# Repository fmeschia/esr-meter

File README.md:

ESR Meter
=========
An Arduino-based battery internal resistance meter.

Introduction
------------
This device measures the internal resistance of a battery by measuring the voltage difference at the battery terminals when a load is applied and then removed. By measuring the difference in voltage and the difference in current, the resistance is readily determined via Ohm's law.

Design goals
------------
* Measure internal resistance for batteries with voltages ranging from a 4-cell NiXX to a 4S LiPo pack
* Resistance range: 1 to 1000 mOhm
* Ability to do 4-wire measurements
* Target precision: 2% ± 1 LSB
* Ability to draw power either from the battery under test, or from a separate battery
* Powered by the Atmel ATMega328P microcontroller (so that it can be prototyped with Arduino)
* Low cost!

Design
------

This device measures the internal resistance by using Ohm's law: R = ∆V/∆I. The battery is first connected to a load, then the load is removed. The voltage at the battery teminals is measured just before removing the load, and just after the load is removed. The current drawn from the battery is also measured, almost simultaneously with the two voltage measurements.

Voltage and current measurement is performed using a 4-wire (Kelvin) technique: current is measured by a sensing resistor along the "hot" high-current path which connects the battery to the load, and voltage is sensed through two "cold" leads, that carry no current. This also allows for internal resistance measurement of the individual cells in a multi-cell battery, as long as the individual cell voltages are available at a balance tap.

One of the problems that must be solved is how to measure voltages (like the two battery under test terminals) which may exceed the ADC reference voltage. The ATMega328P microcontroller can be powered with 5.5V maximum, so if we were to do a direct measurement (battery terminals direct to ADC inputs) we would be only be able to measure a 4-cell NiXX battery... if it's not fully charged.

One possibility to overcome this problem would be to use differential analog amplifiers to bring the voltages within the measurement range. The gain and the baseline of the amplifiers could be adjusted by the micro with digital potentiometers, to adapt to different battery voltages. The drawback is the number of additional components, which influences the cost of the device.

Instead of going this route, we decided to use "AC coupling". The voltages sensed at the battery terminals are filtered through one-pole (RC) low-pass filters, so that their DC component is removed.

If the time constant of the fiter is sufficiently long compared to the load-switching-to-measurement delay, we would only measure the actual change in voltage, with negligible error (compare, in the scope plot below, the yellow DC-coupled voltage at the positive battery terminal with the green AC-coupled signal: 1 ms after the load is switched off, when the measurement is taken, the AC-coupled signal is a very faithful estimate of the voltage difference at the battery terminal).

 vs. AC (green) measure of ∆V")

In order to ensure reasonable precision with low cost, we also decided to reference the ADCs to the internal bandgap voltage reference of the micro. This means that, if we want to meet the 1 Ohm maximum range stated in the design goals, we need to draw less than about 1.1 A (we designed the prototype for 0.8 A).

Such an electronic load can be conveniently built with a LM317 regulator used as a current source. This will be the heart of the "hot" loop. Additionally, the hot loop will also include: 

*  a Schottky diode for protection against reverse polarity
*  an n-channel MOSFET used as a switch
*  a 1 Ohm, 1% precision, current sensing resistor

Mainly because of the LM317 dropout characteristics, the minimum voltage that needs to be applied to the hot loop if we want the design current draw is about 4 V. A lower voltage would lead to a lower current figure, as long as it is enough to correctly bias the BJTs inside the LM317 (after that, the device won't work any more). We tested the circuit with a single LiPo cell discharged to 3.5V, without any problem.

The hot loop is switched on and off by the microcontroller, which we decided to power at 3.3 V with an external clock runing at 8 MHz. The program running on the micro switches on the load for 500 ms, then switches it off for 1500 ms, before starting a new cycle. In this way, the 25% duty cycle helps in keeping the average power dissipation acceptable for a LM317 with a passive heat sink, even when sinking current from a 4S LiPo battery.

The microcontroller also drives a standard HD44780 2x16 parallel-interface LCD display module, to output the result of the internal resistance computation at the end of each 2-second measurement cycle. The measurement is automatically refreshed every 2 seconds, for as long as the unit is powered. 

Power for the circuit may come either directly from the battery under test (requires the use of a LDO regulator and a 3.3 V display module), or from a separate battery.

Making it
---------
The project includes Eagle files for both the schematics and the board. The board was designed as a 2-layer PCB with the same 80x36 mm form factor used by standard 2x16 LCD modules, and with the same mounting hole pattern, so that it can be stacked using 1" standoffs.

The Bill of Materials is also included in the project. Here are some component selection notes:

* it is important for precision to use a 1 Ohm, 1% current sensing resistor (R8 in the schematic);
* the reverse-polarity protection diode used in the hot loop (D1 in the schematic) can be replaced with a more common 1N4001 diode, but this increases the voltage drop along the hot loop and may create problems to the LM317 electronic load. If you plan to build this circuit for single-LiPo or 4S NiXX use, it is best to stick with a Schottky diode;
* the Q1 n-channel MOSFET is not critical, as long as it can reliably switch completely on with a 3.3 V gate-to-source voltage. For single-LiPo or 4 NiXX operation, a low "on" drain-to-source resistance is advisable. The FQP30N06L we suggest in the schematic has just 0.035 Ohms of forward resistance when fully "on".
* any 3.3 V low-dropout linear regulator can be used for single-battery operation. The board is designed for the footprint of a L4931. 
* the LM317 used as a current source requires a heat sink for reliable operation. The sink resistor, R1, will dissipate 1 W and must therefore be sized accordingly.

Other notes:

* the board includes two jumper headers. One, labeled "JP3", determines whether the board will be powered from the battery under test (if closed), or from an external battery (if open). In the latter case, a suitable power source must be provided at the via labeled "VCC-ALT".
* the other jumper, JP1, if closed forces the software running in the ATMega328P to show debug information (sensed voltages and currents) in addition to the resistance value.
* another header, JP2, provides an interface to the serial port of the ATMega328P. It is pin-compatible (but pay attention to the correct orientation!) with the FTDI FT232L breakout board offered by Sparkfun (https://www.sparkfun.com/products/9873). The serial port can be used to upload the software into the microcontroller if an Arduino bootloader is used.

The microcontroller must be programmed with the software found in the esr_meter directory. First the software must be compiled within the Arduino IDE, then it must be burned into the ATmega328P flash memory. There are essentially two options for that:

* if you use a microcontroller with a pre-burned Arduino bootloader, you can install the chip in the PCB, and then program it via the JP2 serial port;
* if your microcontroller doesn't have an Arduino bootleader yet, you need to use an ISP programmer (there are several options –- see https://www.arduino.cc/en/Main/Standalone for example) and burn the Arduino bootloader, then you can upload the software via the JP2 serial port.

Assembly notes:

* the LCD module is to be connected to the board with a short length of 6-lead ribbon cable. The 6 leftmost pins of JP4 go to pins 1 to 6 on the LCD module, and the 6 rightmost pins go to pins 11 to 16.
* the battery under test is to be connected to the "hot" loop through the two plated holes labeled BATT+ and BATT- on the board, of course while respecting the polarity, using two suitable wires; the holes should be able to accommodate up to AWG16. The two voltage sense leads will be soldered to the plated holes labeled S+ and S-; polarity in that case is not important, as the software can accommodate reverse polarity.
* The voltage sense leads do not necessarily need to be soldered to the battery connectors. For multiple-cell LiPo use, they can be soldered to a suitable pitch 2-pin header to sense the individual cells at the balancing connector (see picture below).

The following are some pictures of a specimen of the device:

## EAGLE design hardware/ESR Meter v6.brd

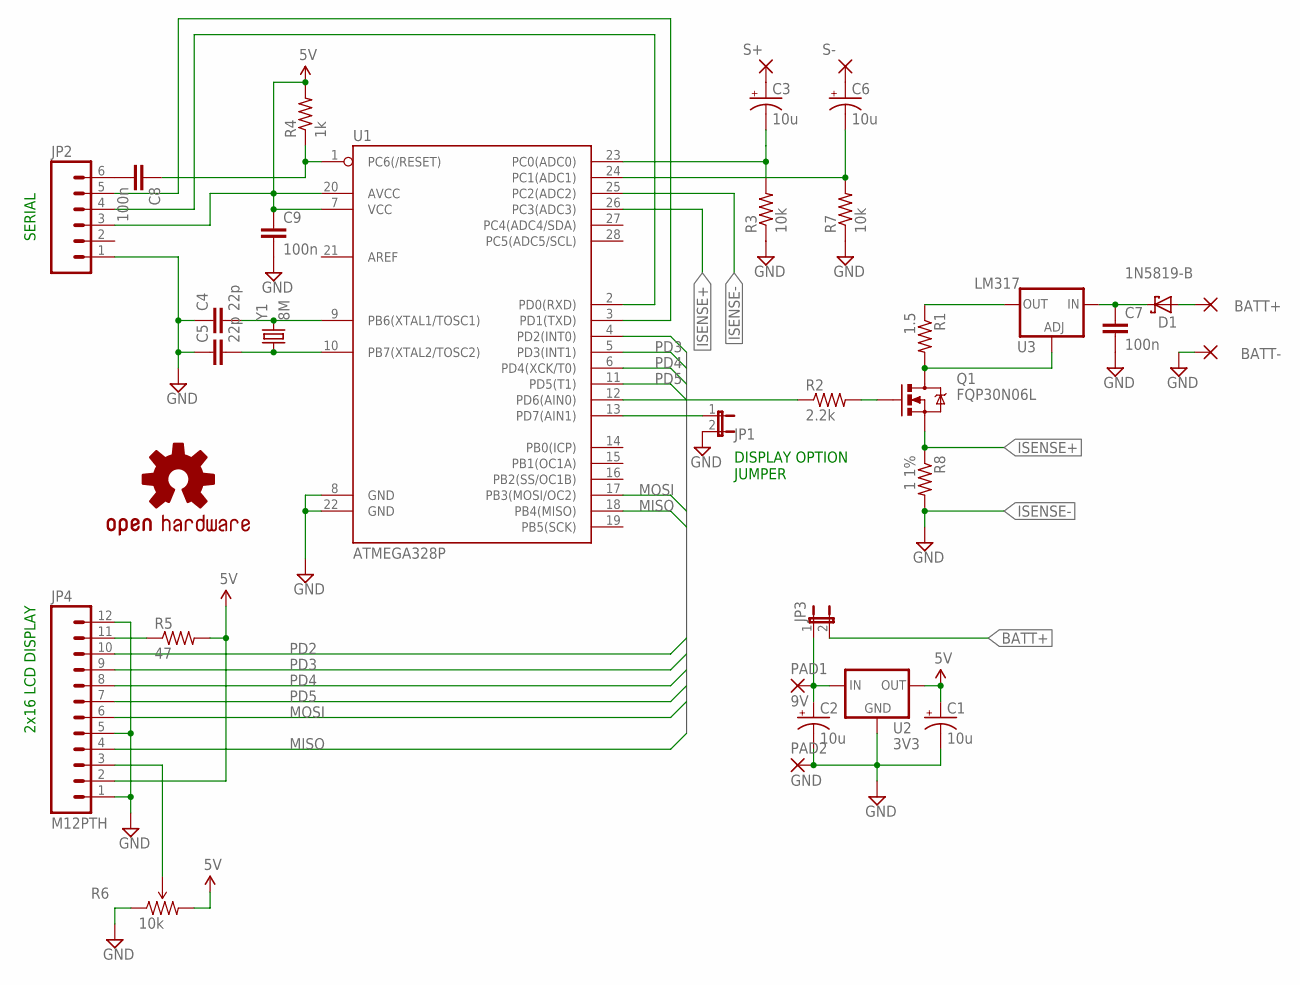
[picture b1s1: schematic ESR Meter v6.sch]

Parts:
BATT+: WIREPAD4,16O1,6; 4,16O1,6
BATT-: WIREPAD4,16O1,6; 4,16O1,6
C1, C2, C3, C6: 10u; CPOL-RADIAL-10UF-25V
C4, C5: 22p; CAP-PTH-SMALLEZ
C7, C8, C9: 100n; CAP-PTH-SMALLEZ
D1: 1N5819-B; DO41-7.6
JP1, JP3: JUMPER-2PTH; 1X02
JP2: M06SILK_FEMALE_PTH; 1X06
JP4: M12PTH; 1X12
LOGO1: OSHW-LOGOM; OSHW-LOGO-M
PAD1: 9V; 1,6/0,9
PAD2: GND; 1,6/0,9
Q1: FQP30N06L; TO220V
R1: 1.5; 0617V
R2: 2.2k; 0207/10
R3, R7: 10k; 0207/10
R4: 1k; 0207/10
R5: 47; 0207/10
R6: 10k; 3386U
R8: 1 1%; 0617V
S+: SENSE; 2,15/1,0
S-: SENSE; 2,15/1,0
U1: ATMEGA328P; DIL28-3
U2: 3V3; L4931
U3: LM317; TO220-ADJ
Y1: 8M; HC49US

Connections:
5V: C1.1 (+), C9.1, JP2.3, JP4.2, R4.2, R5.2, R6.3 (CW), U1.7 (VCC), U1.20 (AVCC), U2.OUT
BATT+: BATT+.1, D1.A, JP3.2
GND: BATT-.1, C1.2 (-), C2.2 (-), C4.1, C5.1, C7.2, C9.2, JP1.2, JP2.1, JP4.1, JP4.5, JP4.12, PAD2.1, R3.1, R6.1 (CCW), R7.1, R8.2, U1.8 (GND), U1.22 (GND), U2.GND
ISENSE+: Q1.3 (S), R8.1, U1.26 (PC3(ADC3))
ISENSE-: U1.25 (PC2(ADC2))
MISO: JP4.4, U1.18 (PB4(MISO))
MOSI: JP4.6, U1.17 (PB3(MOSI/OC2))
unnamed: Q1.1 (G), R2.2
unnamed: Q1.2 (D), R1.2, U3.ADJ
unnamed: R2.1, U1.12 (PD6(AIN0))
unnamed: C3.2 (-), R3.2, U1.23 (PC0(ADC0))
unnamed: C2.1 (+), JP3.1, PAD1.1, U2.IN
unnamed: C4.2, U1.9 (PB6(XTAL1/TOSC1)), Y1.2
unnamed: C5.2, U1.10 (PB7(XTAL2/TOSC2)), Y1.1
unnamed: JP4.3, R6.2 (WIPER)
unnamed: C8.2, JP2.6
unnamed: JP2.5, U1.3 (PD1(TXD))
unnamed: JP2.4, U1.2 (PD0(RXD))
unnamed: C3.1 (+), S+.1
unnamed: JP4.11, R5.1
unnamed: C6.1 (+), S-.1
unnamed: JP1.1, U1.13 (PD7(AIN1))
unnamed: C6.2 (-), R7.2, U1.24 (PC1(ADC1))
unnamed: R1.1, U3.OUT
unnamed: C7.1, D1.C, U3.IN
PD2: JP4.10, U1.4 (PD2(INT0))
PD3: JP4.9, U1.5 (PD3(INT1))
PD4: JP4.8, U1.6 (PD4(XCK/T0))
PD5: JP4.7, U1.11 (PD5(T1))
RESET: C8.1, R4.1, U1.1 (PC6(/RESET))

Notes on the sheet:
2x16 LCD DISPLAY
SERIAL
DISPLAY OPTION JUMPER

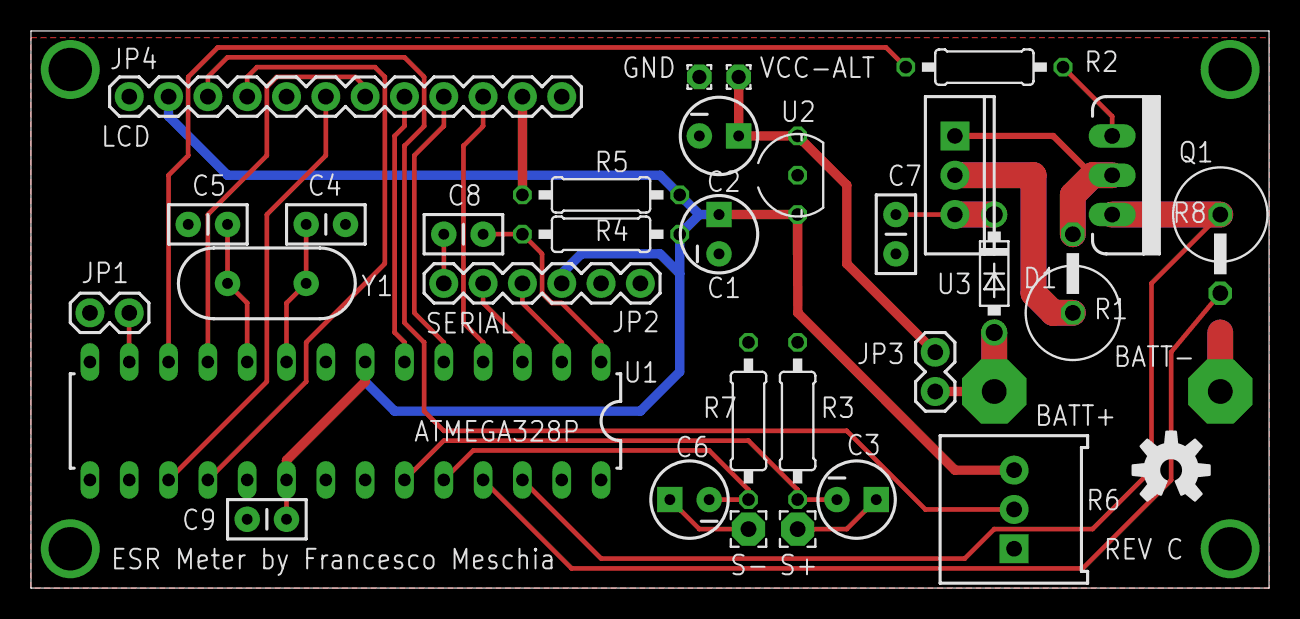
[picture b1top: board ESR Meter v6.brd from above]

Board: 2 copper layers, 80.0 x 36.0 mm, 34 parts (0 on the bottom side), 29 nets.

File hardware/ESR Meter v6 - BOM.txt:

Partlist exported from /Users/franz/Development/Arduino/esr-meter/hardware/ESR Meter v6.sch at 4/2/16 10:34 AM

Part  Value           Device                   Package              Description                                                                                                                                                                                                        PROD_ID    
C1    10u             CAP_POLPTH2              CPOL-RADIAL-10UF-25V Capacitor Polarized                                                                                                                                                                                                           
C2    10u             CAP_POLPTH2              CPOL-RADIAL-10UF-25V Capacitor Polarized                                                                                                                                                                                                           
C3    10u             CAP_POLPTH2              CPOL-RADIAL-10UF-25V Capacitor Polarized                                                                                                                                                                                                           
C4    22p             CAPEZ                    CAP-PTH-SMALLEZ      Capacitor                                                                                                                                                                                                                     
C5    22p             CAPEZ                    CAP-PTH-SMALLEZ      Capacitor                                                                                                                                                                                                                     
C6    10u             CAP_POLPTH2              CPOL-RADIAL-10UF-25V Capacitor Polarized                                                                                                                                                                                                           
C7    100n            CAPEZ                    CAP-PTH-SMALLEZ      Capacitor                                                                                                                                                                                                                     
C8    100n            CAPEZ                    CAP-PTH-SMALLEZ      Capacitor                                                                                                                                                                                                                     
C9    100n            CAPEZ                    CAP-PTH-SMALLEZ      Capacitor                                                                                                                                                                                                                     
D1    1N5819-B        1N5819-B                 DO41-7.6             1.0A SCHOTTKY BARRIER RECTIFIER                                                                                                                                                                                               
JP1                   JUMPER-2PTH              1X02                 Jumper                                                                                                                                                                                                                        
JP2                   M06SILK_FEMALE_PTH       1X06                 Header 6                                                                                                                                                                                                           CONN-08437 
JP3                   JUMPER-2PTH              1X02                 Jumper                                                                                                                                                                                                                        
Q1    FQP30N06L       MOSFET-NCHANNELFQP30N06L TO220V               Common NMOSFET Parts                                                                                                                                                                                               TRANS-10060
R1    1.5             R-US_0617/5V             0617V                RESISTOR, American symbol                                                                                                                                                                                                     
R2    2.2k            R-US_0207/10             0207/10              RESISTOR, American symbol                                                                                                                                                                                                     
R3    10k             R-US_0207/10             0207/10              RESISTOR, American symbol                                                                                                                                                                                                     
R4    1k              R-US_0207/10             0207/10              RESISTOR, American symbol                                                                                                                                                                                                     
R5    47              R-US_0207/10             0207/10              RESISTOR, American symbol                                                                                                                                                                                                     
R6    10k             TRIMPOT-PTH-KNOB         3386U                Various small potentiometers for "set-and-forget" applications                                                                                                                                                                
R7    10k             R-US_0207/10             0207/10              RESISTOR, American symbol                                                                                                                                                                                                     
R8    1 1%            R-US_0617/5V             0617V                RESISTOR, American symbol                                                                                                                                                                                                     
U1    ATMEGA328P      ATMEGA328P_PDIP          DIL28-3              uC used in the Arduino                                                                                                                                                                                                        
U2    3V3             L4931                    L4931                VOLTAGE REGULATOR                                                                                                                                                                                                             
U3    LM317           V_REG_317SINK            TO220-ADJ            Voltage Regulator                                                                                                                                                                                                             
Y1    8M              CRYSTALHC49US            HC49US               Various standard crystals. Proven footprints.

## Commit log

2016-02-15 Renamed files to conform to Arduino IDE needs
2016-02-15 Added Eagle hardware files
2016-02-15 Removed unnecessary library files
2016-02-15 Update library used for L4931
2016-02-15 Moved .gitignore for Eagle in hardware directory
2016-03-29 Rewrote README.md
2016-03-31 Edited README
2016-04-01 Documentation changes
2016-04-05 Added BOM. Minor changes to schematics and board.
2016-04-11 Board revision C, with additional clearance for supply and "HV" (battery) traces
2016-04-12 Further tweaks with trace clearance
2016-05-17 Added serial output (as a form of diagnostic output)
2016-11-28 Improved documentatin
2016-11-28 Doc changes

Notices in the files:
parts and their libraries:
SparkFun-Capacitors: Licensing: Creative Commons ShareAlike 4.0 International - https://creativecommons.org/licenses/by-sa/4.0
